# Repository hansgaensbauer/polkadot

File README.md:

# polkadot
A low cost, standalone LoRa mesh network using STM32 and the SX1276.

## Firmware
The firmware implements a limited (and highly simplified) version of the AODV routing algorithm. Identical nodes running identical firmware can route a mesh automatically and efficiently without outside intervention. Additional nodes (which can also be running "factory" firmware) will route themselves when they power on. 

## Hardware

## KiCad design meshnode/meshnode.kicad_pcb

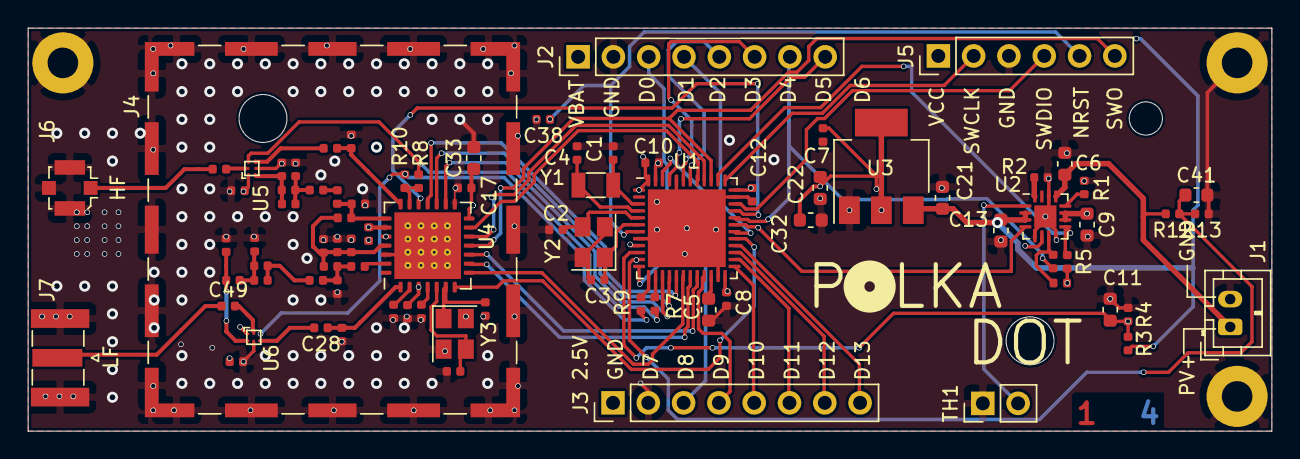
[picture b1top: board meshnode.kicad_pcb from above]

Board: 4 copper layers, 89.5 x 29.0 mm, 88 parts (1 on the bottom side), 71 nets.

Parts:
BT1: Battery_Cell; BatteryHolder_Keystone_1042_1x18650
C1, C2, C3, C4, C15, C16, C24, C39: 15p; C_0402_1005Metric
C5, C9, C13: 4.7u; C_0603_1608Metric
C6, C21, C22: 1u; C_0603_1608Metric
C7, C8, C10, C12, C14, C17, C18, C19, C20, C38: 100n; C_0402_1005Metric
C11, C32, C33, C41: 10u; C_0603_1608Metric
C23: 1.5p; C_0402_1005Metric
C25: 10n; C_0402_1005Metric
C26: 33p; C_0402_1005Metric
C27: 18p; C_0402_1005Metric
C28, C35: 22p; C_0402_1005Metric
C29, C30, C47, C49: 47p; C_0402_1005Metric
C31: 3.3p; C_0402_1005Metric
C34: 4.7p; C_0402_1005Metric
C36: 2.7p; C_0402_1005Metric
C37: 1.2p; C_0402_1005Metric
C40: 1.8p; C_0402_1005Metric
C44: 6.8p; C_0402_1005Metric
C45, C46: 1n; C_0402_1005Metric
H1, H2, H3: MountingHole_Pad; MountingHole_2.2mm_M2_Pad
J1: Conn_01x02_Male; JST_PH_B2B-PH-K_1x02_P2.00mm_Vertical
J2, J3: Conn_01x08_Male; PinHeader_1x08_P2.54mm_Vertical
J4: RF_Shield_Two_Pieces; Laird_Technologies_BMI-S-203-F_26.21x26.21mm
J5: SWD; PinHeader_1x06_P2.54mm_Vertical
J6: Conn_Coaxial; U.FL_Molex_MCRF_73412-0110_Vertical
J7: Conn_Coaxial; SMA_Samtec_SMA-J-P-X-ST-EM1_EdgeMount
L1: 2.2n; L_0402_1005Metric
L2, L3: 33n; L_0402_1005Metric
L4: 18n; L_0402_1005Metric
L8: 10n; L_0402_1005Metric
L9: 12n; L_0402_1005Metric
L10: 6.2n; L_0402_1005Metric
L11: 15n; L_0402_1005Metric
R1: 1.18k; R_0402_1005Metric
R2: 1.13k; R_0402_1005Metric
R3, R4, R12: 1Meg; R_0402_1005Metric
R5, R6, R11: 1k; R_0402_1005Metric
R7, R8, R9, R10: 220; R_0402_1005Metric
R13: 100k; R_0402_1005Metric
TH1: 10k; PinHeader_1x02_P2.54mm_Vertical
U1: STM32F401CCUx; QFN-48-1EP_7x7mm_P0.5mm_EP5.6x5.6mm
U2: BQ24074RGT; VQFN-16-1EP_3x3mm_P0.5mm_EP1.6x1.6mm
U3: AZ1117-2.5; SOT-223-3_TabPin2
U4: SX1276; QFN-28-1EP_6x6mm_P0.65mm_EP4.8x4.8mm_ThermalVias
U5, U6: SKY13453-385LF; SKY13453
Y1: 32.786k; Crystal_SMD_3215-2Pin_3.2x1.5mm
Y2: 16Meg; Crystal_SMD_SeikoEpson_TSX3225-4Pin_3.2x2.5mm
Y3: 32Meg; Crystal_SMD_SeikoEpson_TSX3225-4Pin_3.2x2.5mm

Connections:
+2V5: C7.2, C8.2, C10.2, C12.2, C17.2, C19.2, C20.2, C22.1, C32.1, C33.1, C45.1, C46.1, J3.1, J5.1, R5.1, R6.1, U1.1, U1.9, U1.24, U1.36, U1.48, U3.2, U4.3, U4.14, U4.24, U5.1, U6.1
+4V: C9.1, U2.6, U2.10, U2.11
+BATT: BT1.1, C13.1, C21.1, J2.1, R3.2, U2.2, U2.3, U3.3
/CHG_~CE: U1.31, U2.4
/CS_X: U1.33, U4.19
/DIO0: U1.18, U4.8
/DIO1: U1.19, U4.9
/DIO2: U1.20, U4.10
/DIO4: U1.40, U4.12
/DIO5: U1.41, U4.13
/GPIO_0: J2.3, U1.12
/GPIO_1: J2.4, U1.30
/GPIO_2: J2.5, U1.42
/GPIO_3: J2.6, U1.43
/GPIO_5: J2.8, U1.45
/GPIO_6: J3.3, U1.46
/GPIO_7: J3.4, U1.21
/GPIO_8: J3.5, U1.25
/GPIO_9: J3.6, U1.26
/GPIO_10: J3.7, U1.27
/GPIO_11: J3.8, U1.28
/MISO: U1.16, U4.17
/MOSI: U1.17, U4.18
/NRST: C38.1, J5.5, U1.7
/RST: U1.29, U4.7
/RXTX: R8.1, R10.1, U4.20
/RXTX_HF: R7.1, U1.14
/RXTX_LF: R9.1, U1.13
/SCK: U1.15, U4.16
/SWCLK: J5.2, U1.37
/SWDIO: J5.4, U1.34
/SWO: J5.6, U1.39, U4.11
/~CHG: R5.2, U1.38, U2.9
/~PGOOD: J2.7, R11.2, U1.32
GND: BT1.2, C1.1, C2.1, C3.2, C4.2, C5.2, C6.1, C7.1, C8.1, C9.2, C10.1, C11.2, C12.1, C13.2, C14.2, C15.1, C16.2, C17.1, C18.2, C19.1, C20.1, C21.2, C22.2, C23.2, C24.2, C25.2, C29.2, C30.2, C31.2, C32.2, C33.2, C34.1, C38.2, C39.2, C40.1, C41.2, C44.1, C45.2, C46.2, H1.1, H2.1, H3.1, J1.2, J2.2, J3.2, J4.1, J5.3, J6.2, J7.2, L4.2, R1.2, R2.1, R4.1, R13.1, TH1.1, U1.8, U1.23, U1.35, U1.44, U1.47, U1.49, U2.5, U2.8, U2.14, U2.17, U3.1, U4.15, U4.23, U4.26, U4.29, U5.3, U6.3, Y2.2, Y2.4, Y3.2, Y3.4
unnamed: C1.2, U1.3, Y1.1
unnamed: C2.2, U1.5, Y2.3
unnamed: C3.1, U1.6, Y2.1
unnamed: C4.1, U1.4, Y1.2
unnamed: C5.1, U1.22
unnamed: C11.1, R3.1, R4.2, U1.10
unnamed: C14.1, U4.4
unnamed: C15.2, U4.5, Y3.3
unnamed: C16.1, U4.6, Y3.1
unnamed: C18.1, U4.2
unnamed: C23.1, C26.2, L3.1, U4.22
unnamed: C24.1, C27.1, L1.2, L2.2
unnamed: C25.1, C29.1, C30.1, L2.1, L3.2, U4.25
unnamed: C26.1, L8.1
unnamed: C27.2, C36.1, L9.1
unnamed: C28.1, L4.1, U4.1
unnamed: C28.2, U6.4
unnamed: C31.1, C35.1, U4.21
unnamed: C34.2, C37.1, L8.2, L10.1
unnamed: C35.2, U5.4
unnamed: C36.2, C39.1, L9.2, L11.1
unnamed: C37.2, C40.2, L10.2, U5.2
unnamed: C41.1, R12.1, R13.2, U1.11
unnamed: C44.2, L11.2, U6.2
unnamed: C47.1, J6.1
unnamed: C47.2, U5.6
unnamed: C49.1, J7.1
unnamed: C49.2, U6.6
unnamed: L1.1, U4.27
unnamed: R1.1, U2.12
unnamed: R2.2, U2.16
unnamed: R7.2, R8.2, U5.5
unnamed: R9.2, R10.2, U6.5
unnamed: R6.2, R11.1, U2.7
unnamed: TH1.2, U2.1
VPP: C6.2, J1.1, R12.2, U2.13

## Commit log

2021-08-21 Added polkadot files
    Includes both hardware and firmware
